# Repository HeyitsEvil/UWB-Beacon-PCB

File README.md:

# UWB-Beacon-PCB
HKUST ELEC 3300 Project. The PCB is used for a UWB tracking project

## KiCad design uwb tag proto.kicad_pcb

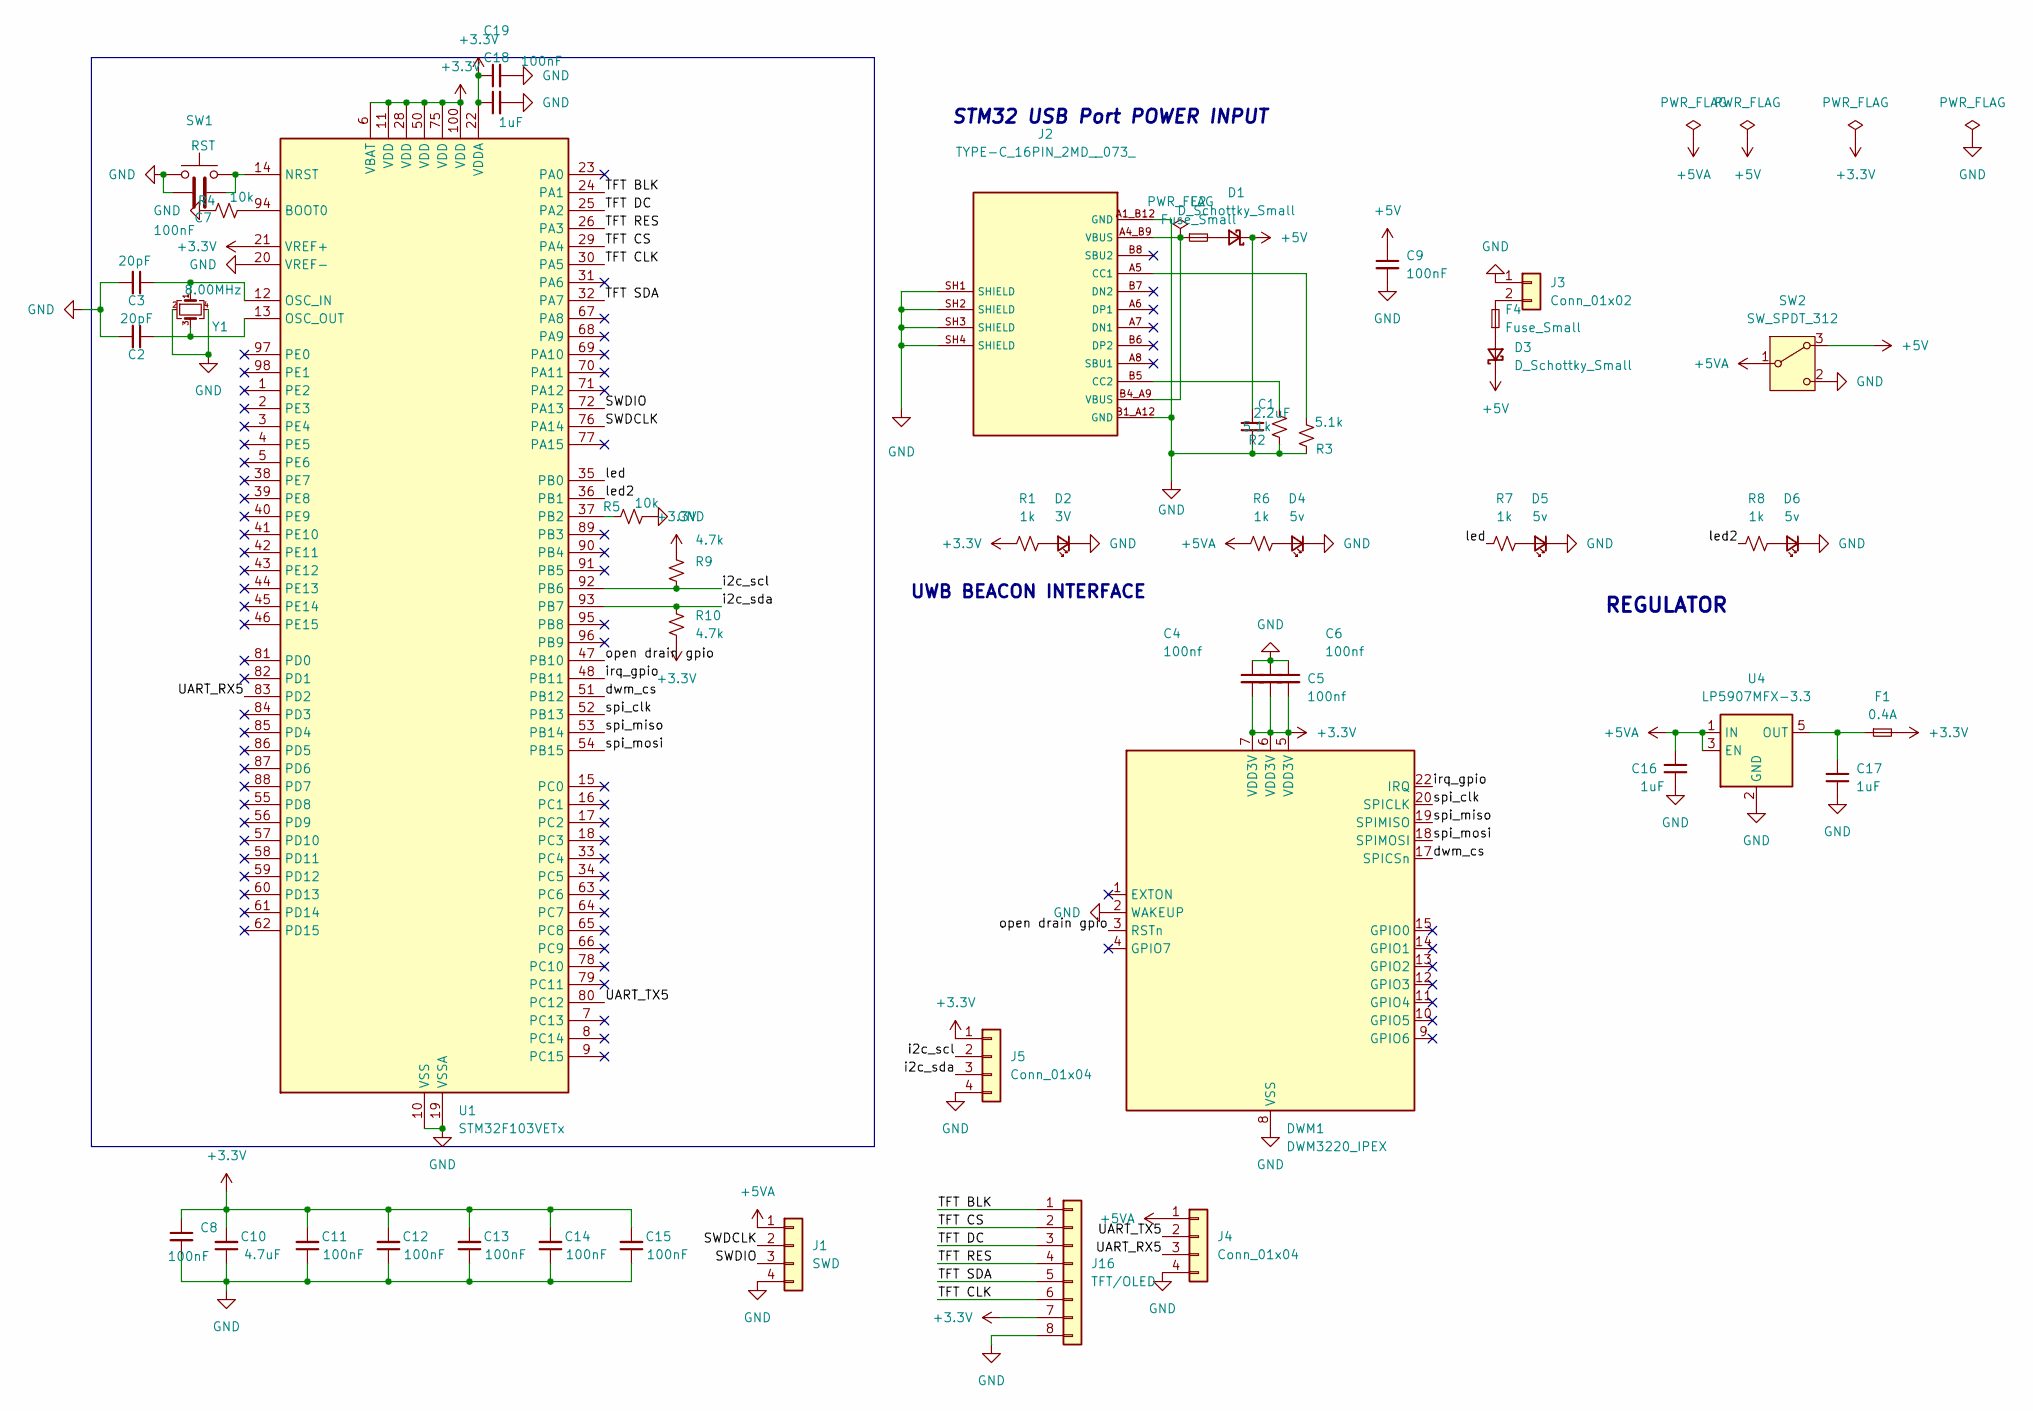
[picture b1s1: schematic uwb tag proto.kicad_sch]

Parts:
C1: 2.2uF; C_0603_1608Metric
C2, C3: 20pF; C_0805_2012Metric
C4, C5, C6: 100nf; C_0603_1608Metric
C7, C8, C9, C11, C12, C13, C14, C15, C19: 100nF; C_0603_1608Metric
C10: 4.7uF; C_0603_1608Metric
C16, C17, C18: 1uF; C_0603_1608Metric
D1, D3: D_Schottky_Small; D_SMA_Handsoldering
D2: 3V; LED_0603_1608Metric
D4, D5, D6: 5v; LED_0603_1608Metric
DWM1: DWM3220_IPEX
F1: 0.4A; R_0603_1608Metric
F2, F4: Fuse_Small; R_0603_1608Metric
J1: SWD; JST_XH_B4B-XH-A_1x04_P2.50mm_Vertical
J2: TYPE-C_16PIN_2MD__073_; SHOUHAN_ TYPEC 16PIN; PARTREV A
J3: Conn_01x02; JST_XH_B2B-XH-A_1x02_P2.50mm_Vertical
J4, J5: Conn_01x04; JST_XH_B4B-XH-A_1x04_P2.50mm_Vertical
J16: TFT/OLED; PinSocket_1x08_P2.54mm_Vertical
R1, R6, R7, R8: 1k; R_0603_1608Metric
R2, R3: 5.1k; R_0603_1608Metric
R4, R5: 10k; R_0603_1608Metric
R9, R10: 4.7k; R_0603_1608Metric
SW1: RST; SW_Push
SW2: SW_SPDT_312; SW_Slide-03_Wuerth-WS-SLTV_10x2.5x6.4_P2.54mm
U1: STM32F103VETx; LQFP-100_14x14mm_P0.5mm
U4: LP5907MFX-3.3; SOT-23-5
Y1: 8.00MHz; Crystal_SMD_3225-4Pin_3.2x2.5mm

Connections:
+3.3V: C4.2, C5.2, C6.2, C8.1, C10.2, C11.2, C12.2, C13.2, C14.2, C15.2, C18.1, C19.1, DWM1.5 (VDD3V), DWM1.6 (VDD3V), DWM1.7 (VDD3V), F1.2, J5.1, J16.7, R1.1, R9.1, R10.2, U1.6 (VBAT), U1.11 (VDD), U1.21 (VREF+), U1.22 (VDDA), U1.28 (VDD), U1.50 (VDD), U1.75 (VDD), U1.100 (VDD)
+5V: C1.2, C9.1, D1.1 (K), D3.1 (K), SW2.3 (A)
+5VA: C16.1, J1.1, J4.1, R6.1, SW2.1 (B), U4.1 (IN), U4.3 (EN)
/SWDCLK: J1.2, U1.76 (PA14)
/SWDIO: J1.3, U1.72 (PA13)
/TFT BLK: J16.1, U1.24 (PA1)
/TFT CLK: J16.6, U1.30 (PA5)
/TFT CS: J16.2, U1.29 (PA4)
/TFT DC: J16.3, U1.25 (PA2)
/TFT RES: J16.4, U1.26 (PA3)
/TFT SDA: J16.5, U1.32 (PA7)
/UART_RX5: J4.3, U1.83 (PD2)
/UART_TX5: J4.2, U1.80 (PC12)
/dwm_cs: DWM1.17 (SPICSn), U1.51 (PB12)
/i2c_scl: J5.2, R9.2, U1.92 (PB6)
/i2c_sda: J5.3, R10.1, U1.93 (PB7)
/irq_gpio: DWM1.22 (IRQ), U1.48 (PB11)
/led: R7.1, U1.35 (PB0)
/led2: R8.1, U1.36 (PB1)
/open drain gpio: DWM1.3 (RSTn), U1.47 (PB10)
/spi_clk: DWM1.20 (SPICLK), U1.52 (PB13)
/spi_miso: DWM1.19 (SPIMISO), U1.53 (PB14)
/spi_mosi: DWM1.18 (SPIMOSI), U1.54 (PB15)
GND: C1.1, C2.2, C3.2, C4.1, C5.1, C6.1, C7.1, C8.2, C9.2, C10.1, C11.1, C12.1, C13.1, C14.1, C15.1, C16.2, C17.2, C18.2, C19.2, D2.1 (K), D4.1 (K), D5.1 (K), D6.1 (K), DWM1.2 (WAKEUP), DWM1.8 (VSS), DWM1.16 (VSS), DWM1.21 (VSS), DWM1.23 (VSS), DWM1.24 (VSS), J1.4, J2.A1_B12 (GND), J2.B1_A12 (GND), J2.SH1 (SHIELD), J2.SH2 (SHIELD), J2.SH3 (SHIELD), J2.SH4 (SHIELD), J3.1, J4.4, J5.4, J16.8, R2.2, R3.2, R4.1, R5.2, SW1.1, SW2.2 (C), U1.10 (VSS), U1.19 (VSSA), U1.20 (VREF-), U1.27 (VSS), U1.49 (VSS), U1.74 (VSS), U1.99 (VSS), U4.2 (GND), Y1.2, Y1.4
unnamed: D1.2 (A), F2.2
unnamed: D2.2 (A), R1.2
unnamed: D3.2 (A), F4.1
unnamed: D4.2 (A), R6.2
unnamed: D5.2 (A), R7.2
unnamed: D6.2 (A), R8.2
unnamed: F2.1, J2.A4_B9 (VBUS), J2.B4_A9 (VBUS)
unnamed: J2.A5 (CC1), R3.1
unnamed: J2.B5 (CC2), R2.1
unnamed: F4.2, J3.2
unnamed: R4.2, U1.94 (BOOT0)
unnamed: C7.2, SW1.2, U1.14 (NRST)
unnamed: C3.1, U1.12 (OSC_IN), Y1.1
unnamed: C2.1, U1.13 (OSC_OUT), Y1.3
unnamed: R5.1, U1.37 (PB2)
unnamed: C17.1, F1.1, U4.5 (OUT)

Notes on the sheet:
UWB BEACON INTERFACE
STM32 USB Port POWER INPUT
REGULATOR

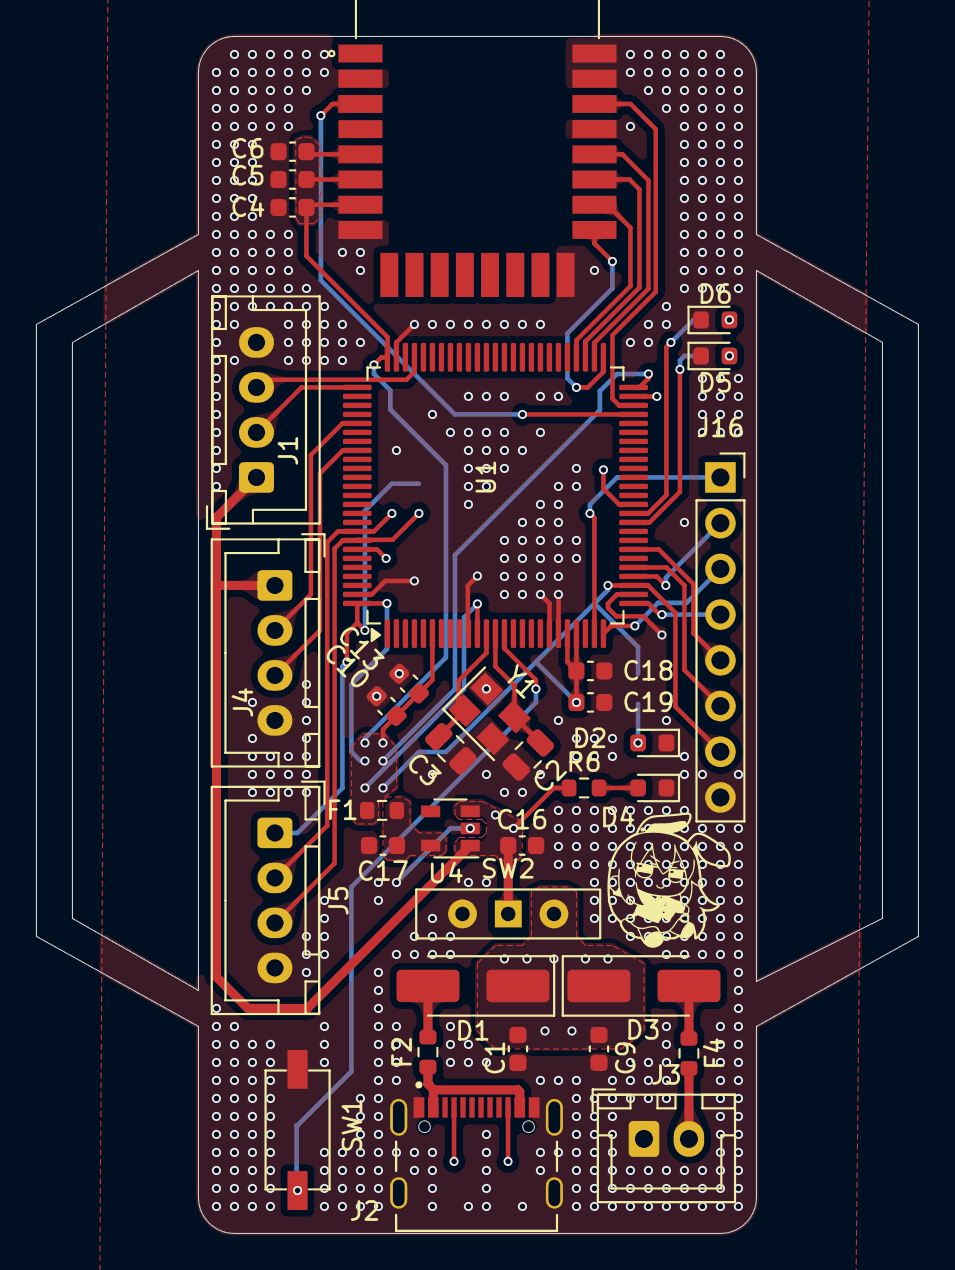
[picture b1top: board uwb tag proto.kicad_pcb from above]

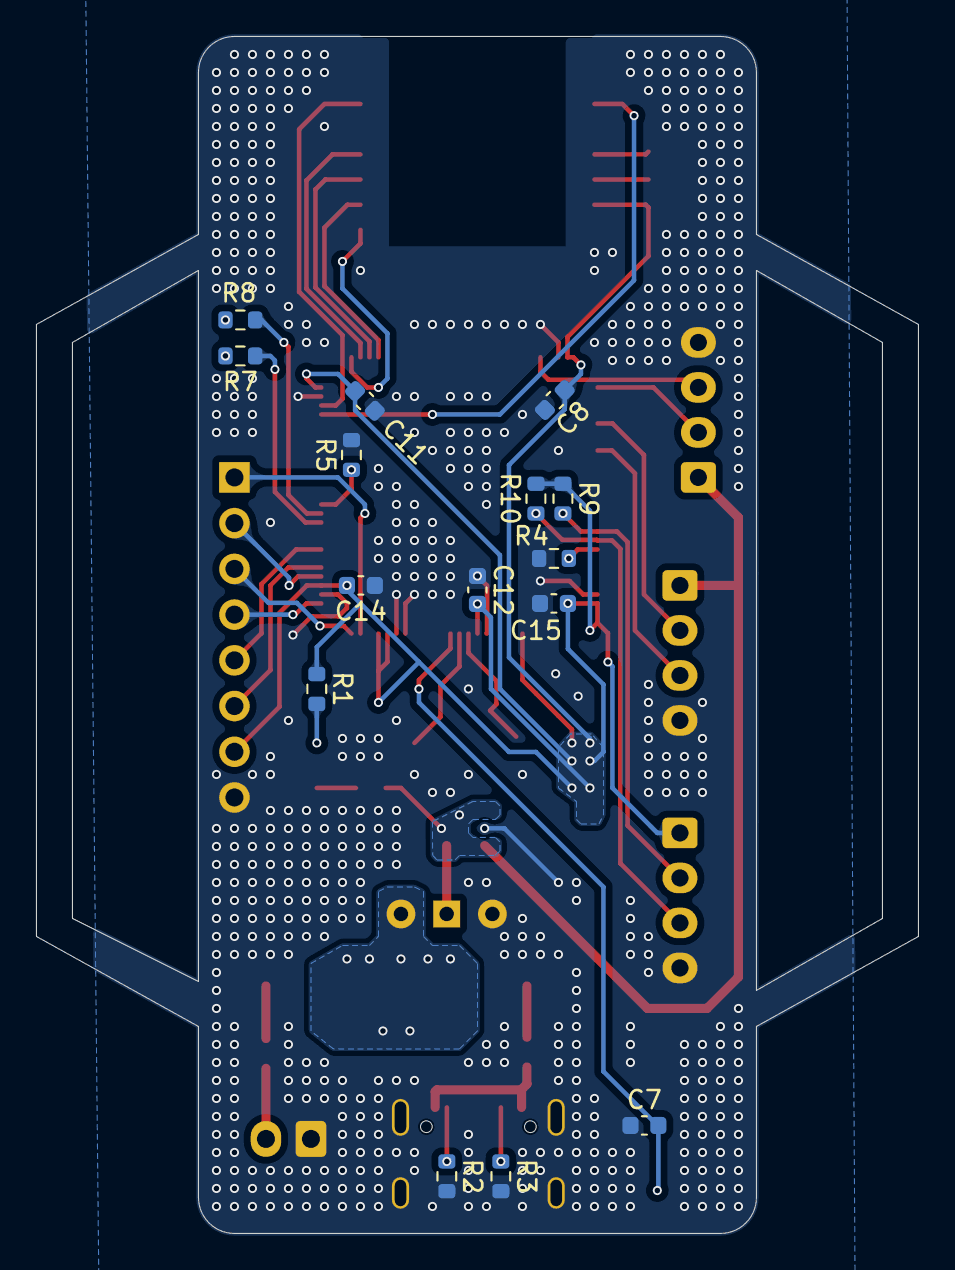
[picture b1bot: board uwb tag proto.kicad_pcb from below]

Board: 2 copper layers, 49.0 x 66.5 mm, 50 parts (15 on the bottom side), 40 nets.
